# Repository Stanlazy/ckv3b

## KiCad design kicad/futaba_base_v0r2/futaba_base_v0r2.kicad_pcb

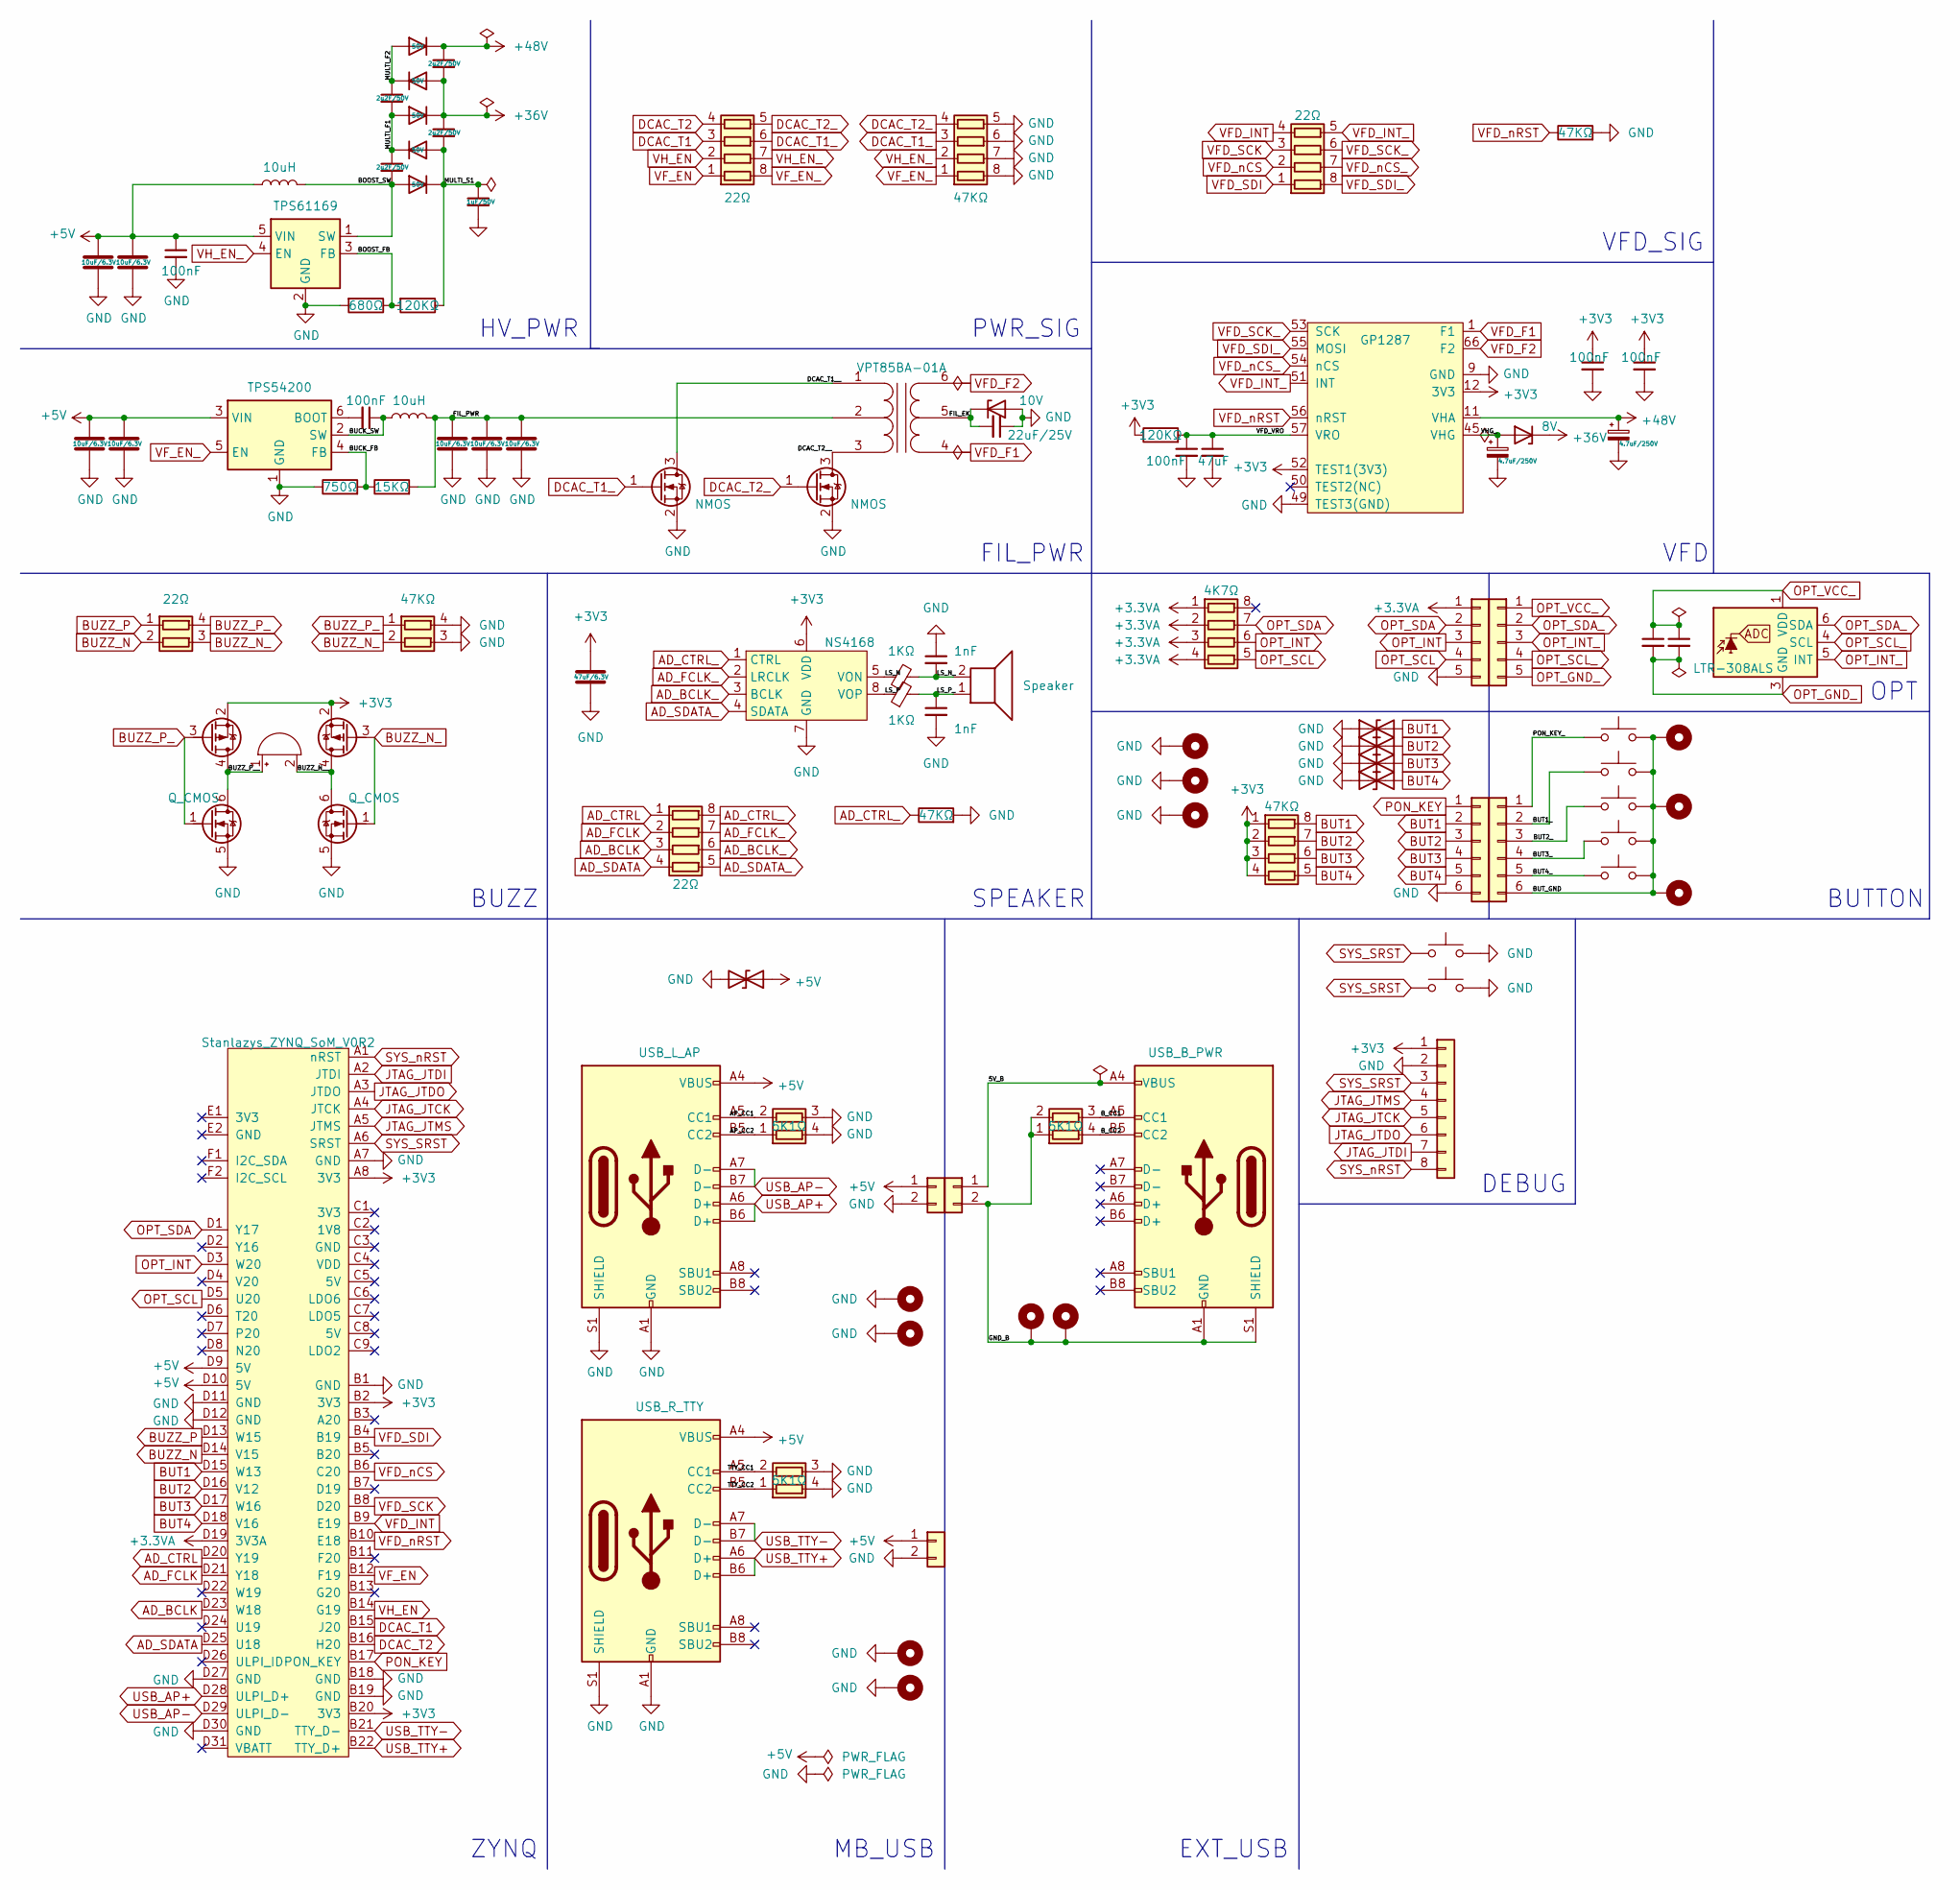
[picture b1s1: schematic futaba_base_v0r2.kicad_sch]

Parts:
A1: Stanlazys_ZYNQ_SoM_V0R2
BZ1: Buzzer; PUIAudio_SMT_0825_S_4_R
C1, C2, C3, C4: 2u2F/50V; C_0805_2012Metric
C5: 1uF/50V; C_0805_2012Metric
C6, C9, C10, C11, C19, C23: 100nF; C_0402_1005Metric
C7, C8, C14, C15, C16, C17, C18: 10uF/6.3V; C_0603_1608Metric
C12: 22uF/25V; C_0805_2012Metric
C13, C21: 4.7uF/250V; CP_Elec_6.3x5.7
C20: 47uF; C_0805_2012Metric
C22: 4u7F; C_0402_1005Metric
C24, C26: 1nF; C_0402_1005Metric
C25: 47uF/6.3V; C_0805_2012Metric
D1, D2, D3, D4, D5: 50V; D_SOD-123F
D6: 10V; D_SOD-123F
D7: 8V; D_SOD-123F
D8, D9, D10, D11: D_TVS; R_0201_0603Metric
D12: D_TVS; D_SOD-323
DS1: GP1287; Futaba_GP1287
FB1, FB2: 1KΩ; L_0402_1005Metric
H1, H2, H3, H4, H5, H6, H7, H8, H9, H10, H11, H12: MountingHole_Pad; MountingHole_PinHeader_2.54_3D
J1: Conn_01x05; opt_mb
J2: Conn_01x05; opt_ph
J3: Conn_01x06; but_mb
J4: Conn_01x06; but_ph
J5: Conn_01x08; PinHeader_1x08_P2.54mm_Vertical
J6: USB_L_AP; USB_C_Receptacle_HRO_TYPE-C-31-M-12
J7, J11: Conn_01x02; usb_mb
J8: Conn_01x02; usb_ph
J9: USB_B_PWR; USB_C_Receptacle_HRO_TYPE-C-31-M-12
J10: USB_R_TTY; USB_C_Receptacle_HRO_TYPE-C-31-M-12
L1, L2: 10uH; L_Abracon_ASPI-0630LR
LS1: Speaker; PinHeader_1x02_P2.54mm_Vertical
Q1, Q2: NMOS; SOT-23
Q3, Q4: Q_CMOS; SOT-23-6
R1, R7: 47KΩ; R_0402_1005Metric
R2: 680Ω; R_0402_1005Metric
R3, R4: 120KΩ; R_0402_1005Metric
R5: 750Ω; R_0402_1005Metric
R6: 15KΩ; R_0402_1005Metric
RN1, RN3, RN7: 22Ω; R_Array_Convex_4x0402
RN2, RN8: 47KΩ; R_Array_Convex_4x0402
RN4: 22Ω; R_Array_Convex_2x0402
RN5: 47KΩ; R_Array_Convex_2x0402
RN6: 4K7Ω; R_Array_Convex_4x0402
RN9, RN10, RN11: 5K1Ω; R_Array_Convex_2x0402
SW1, SW2, SW3, SW4, SW5, SW6: SW_Push; SW_Push_1P1T_NO_6x6mm_H9.5mm
SW7: SW_Push; SW_SPST_CK_RS282G05A3
T1: VPT85BA-01A; VPT85xx
U1: TPS61169; SOT-353_SC-70-5
U2: TPS54200; SOT-23-6
U3: LTR-308ALS
U4: NS4168; HSOP-8-1EP_3.9x4.9mm_P1.27mm_EP2.3x2.3mm

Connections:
+3.3VA: A1.D19 (3V3A), J1.1, RN6.1 (R1.1), RN6.2 (R2.1), RN6.3 (R3.1), RN6.4 (R4.1)
+3V3: A1.A8 (3V3), A1.B2 (3V3), A1.B20 (3V3), C9.1, C10.1, C25.1, DS1.12 (3V3), DS1.52 (TEST1(3V3)), DS1.60 (3V3), J5.1, Q3.2 (S2), Q4.2 (S2), R4.1, RN8.1 (R1.1), RN8.2 (R2.1), RN8.3 (R3.1), RN8.4 (R4.1), U4.6 (VDD)
+5V: A1.D9 (5V), A1.D10 (5V), C6.1, C7.1, C8.1, C14.1, C15.1, D12.1 (A1), J6.A4 (VBUS), J6.A9 (VBUS), J6.B4 (VBUS), J6.B9 (VBUS), J7.1, J10.A4 (VBUS), J10.A9 (VBUS), J10.B4 (VBUS), J10.B9 (VBUS), J11.1, L1.1, U1.5 (VIN), U2.3 (VIN)
+36V: C1.2, C3.1, D2.2 (A), D3.1 (K), D7.1 (K)
+48V: C1.1, C13.1, D1.1 (K), DS1.11 (VHA)
/5V_B: J8.1, J9.A4 (VBUS), J9.A9 (VBUS), J9.B4 (VBUS), J9.B9 (VBUS)
/AP_CC1: J6.A5 (CC1), RN9.2 (R2.1)
/AP_CC2: J6.B5 (CC2), RN9.1 (R1.1)
/BOOST_FB: R2.1, R3.2, U1.3 (FB)
/BOOST_SW: C4.2, D5.2 (A), L1.2, U1.1 (SW)
/BUCK_FB: R5.2, R6.1, U2.4 (FB)
/BUCK_SW: C11.1, L2.1, U2.2 (SW)
/BUT1_: J4.2, SW2.1
/BUT2_: J4.3, SW3.1
/BUT3_: J4.4, SW4.1
/BUT4_: J4.5, SW5.1
/BUT_GND: H1.1, H4.1, H6.1, J4.6, SW1.2, SW2.2, SW3.2, SW4.2, SW5.2
/BUZZ_N__: BZ1.2 (+), Q4.4 (D2), Q4.6 (D1)
/BUZZ_P__: BZ1.1 (-), Q3.4 (D2), Q3.6 (D1)
/B_CC1: J9.A5 (CC1), RN10.3 (R2.2)
/B_CC2: J9.B5 (CC2), RN10.4 (R1.2)
/DCAC_T1__: Q1.3 (D), T1.1 (PR1)
/DCAC_T2__: Q2.3 (D), T1.3 (PR2)
/FIL_EK: C12.2, D6.1 (K), T1.5 (S2)
/FIL_PWR: C16.1, C17.1, C18.1, L2.2, R6.2, T1.2 (PM)
/GND_B: H8.1, H9.1, J8.2, J9.A1 (GND), J9.A12 (GND), J9.B1 (GND), J9.B12 (GND), J9.S1 (SHIELD), RN10.1 (R1.1), RN10.2 (R2.1)
/LS_N: FB1.1, U4.5 (VON)
/LS_N_: C24.2, FB1.2, LS1.2
/LS_P: FB2.1, U4.8 (VOP)
/LS_P_: C26.1, FB2.2, LS1.1
/MULTI_F1: C2.2, C4.1, D3.2 (A), D4.1 (K)
/MULTI_F2: C2.1, D1.2 (A), D2.1 (K)
/MULTI_S1: C3.2, C5.1, D4.2 (A), D5.1 (K), R3.1
/PON_KEY_: J4.1, SW1.1
/TTY_CC1: J10.A5 (CC1), RN11.2 (R2.1)
/TTY_CC2: J10.B5 (CC2), RN11.1 (R1.1)
/VFD_VRO: C19.1, C20.1, DS1.57 (VRO), R4.2
/VHG_: C21.1, D7.2 (A), DS1.45 (VHG)
AD_BCLK: A1.D23 (W18), RN7.3 (R3.1)
AD_BCLK_: RN7.6 (R3.2), U4.3 (BCLK)
AD_CTRL: A1.D20 (Y19), RN7.1 (R1.1)
AD_CTRL_: R7.1, RN7.8 (R1.2), U4.1 (CTRL)
AD_FCLK: A1.D21 (Y18), RN7.2 (R2.1)
AD_FCLK_: RN7.7 (R2.2), U4.2 (LRCLK)
AD_SDATA: A1.D25 (U18), RN7.4 (R4.1)
AD_SDATA_: RN7.5 (R4.2), U4.4 (SDATA)
BUT1: A1.D15 (W13), D8.2 (A2), J3.2, RN8.8 (R1.2)
BUT2: A1.D16 (V12), D9.2 (A2), J3.3, RN8.7 (R2.2)
BUT3: A1.D17 (W16), D10.2 (A2), J3.4, RN8.6 (R3.2)
BUT4: A1.D18 (V16), D11.2 (A2), J3.5, RN8.5 (R4.2)
BUZZ_N: A1.D14 (V15), RN4.2 (R2.1)
BUZZ_N_: Q4.1 (G1), Q4.3 (G2), RN4.3 (R2.2), RN5.2 (R2.1)
BUZZ_P: A1.D13 (W15), RN4.1 (R1.1)
BUZZ_P_: Q3.1 (G1), Q3.3 (G2), RN4.4 (R1.2), RN5.1 (R1.1)
DCAC_T1: A1.B15 (J20), RN1.3 (R3.1)
DCAC_T1_: Q1.1 (G), RN1.6 (R3.2), RN2.3 (R3.1)
DCAC_T2: A1.B16 (H20), RN1.4 (R4.1)
DCAC_T2_: Q2.1 (G), RN1.5 (R4.2), RN2.4 (R4.1)
GND: A1.A7 (GND), A1.B1 (GND), A1.B18 (GND), A1.B19 (GND), A1.D11 (GND), A1.D12 (GND), A1.D27 (GND), A1.D30 (GND), C5.2, C6.2, C7.2, C8.2, C9.2, C10.2, C12.1, C13.2, C14.2, C15.2, C16.2, C17.2, C18.2, C19.2, C20.2, C21.2, C24.1, C25.2, C26.2, D6.2 (A), D8.1 (A1), D9.1 (A1), D10.1 (A1), D11.1 (A1), D12.2 (A2), DS1.9 (GND), DS1.10 (GND), DS1.47 (GND), DS1.49 (TEST3(GND)), DS1.61 (GND), H2.1, H3.1, H5.1, H7.1, H10.1, H11.1, H12.1, J1.5, J3.6, J5.2, J6.A1 (GND), J6.A12 (GND), J6.B1 (GND), J6.B12 (GND), J6.S1 (SHIELD), J7.2, J10.A1 (GND), J10.A12 (GND), J10.B1 (GND), J10.B12 (GND), J10.S1 (SHIELD), J11.2, Q1.2 (S), Q2.2 (S), Q3.5 (S1), Q4.5 (S1), R1.2, R2.2, R5.1, R7.2, RN2.5 (R4.2), RN2.6 (R3.2), RN2.7 (R2.2), RN2.8 (R1.2), RN5.3 (R2.2), RN5.4 (R1.2), RN9.3 (R2.2), RN9.4 (R1.2), RN11.3 (R2.2), RN11.4 (R1.2), SW6.2, SW7.2, U1.2 (GND), U2.1 (GND), U4.7 (GND), U4.9 (GND)
JTAG_JTCK: A1.A4 (JTCK), J5.5
JTAG_JTDI: A1.A2 (JTDI), J5.7
JTAG_JTDO: A1.A3 (JTDO), J5.6
JTAG_JTMS: A1.A5 (JTMS), J5.4
unnamed: C11.2, U2.6 (BOOT)
OPT_GND_: C22.2, C23.2, J2.5, U3.3 (GND)
OPT_INT: A1.D3 (W20), J1.3, RN6.6 (R3.2)
OPT_INT_: J2.3, U3.5 (INT)
OPT_SCL: A1.D5 (U20), J1.4, RN6.5 (R4.2)
OPT_SCL_: J2.4, U3.4 (SCL)
OPT_SDA: A1.D1 (Y17), J1.2, RN6.7 (R2.2)
OPT_SDA_: J2.2, U3.6 (SDA)
OPT_VCC_: C22.1, C23.1, J2.1, U3.1 (VDD)
PON_KEY: A1.B17 (PON_KEY), J3.1
SYS_SRST: A1.A6 (SRST), J5.3, SW6.1, SW7.1
SYS_nRST: A1.A1 (nRST), J5.8
USB_AP+: A1.D28 (ULPI_D+), J6.A6 (D+), J6.B6 (D+)
USB_AP-: A1.D29 (ULPI_D-), J6.A7 (D-), J6.B7 (D-)
USB_TTY+: A1.B22 (TTY_D+), J10.A6 (D+), J10.B6 (D+)
USB_TTY-: A1.B21 (TTY_D-), J10.A7 (D-), J10.B7 (D-)
VFD_F1: DS1.1 (F1), DS1.2 (F1), DS1.3 (F1), DS1.4 (F1), T1.4 (S1)
VFD_F2: DS1.66 (F2), DS1.67 (F2), DS1.68 (F2), DS1.69 (F2), T1.6 (S2)
VFD_INT: A1.B9 (E19), RN3.4 (R4.1)
VFD_INT_: DS1.51 (INT), RN3.5 (R4.2)
VFD_SCK: A1.B8 (D20), RN3.3 (R3.1)
VFD_SCK_: DS1.53 (SCK), RN3.6 (R3.2)
VFD_SDI: A1.B4 (B19), RN3.1 (R1.1)
VFD_SDI_: DS1.55 (MOSI), RN3.8 (R1.2)
VFD_nCS: A1.B6 (C20), RN3.2 (R2.1)
VFD_nCS_: DS1.54 (nCS), RN3.7 (R2.2)
VFD_nRST: A1.B10 (E18), DS1.56 (nRST), R1.1
VF_EN: A1.B12 (F19), RN1.1 (R1.1)
VF_EN_: RN1.8 (R1.2), RN2.1 (R1.1), U2.5 (EN)
VH_EN: A1.B14 (G19), RN1.2 (R2.1)
VH_EN_: RN1.7 (R2.2), RN2.2 (R2.1), U1.4 (EN)

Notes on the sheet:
SPEAKER
BUZZ
ZYNQ
DEBUG
VFD
EXT_USB
PWR_SIG
HV_PWR
OPT
MB_USB
FIL_PWR
VFD_SIG
BUTTON

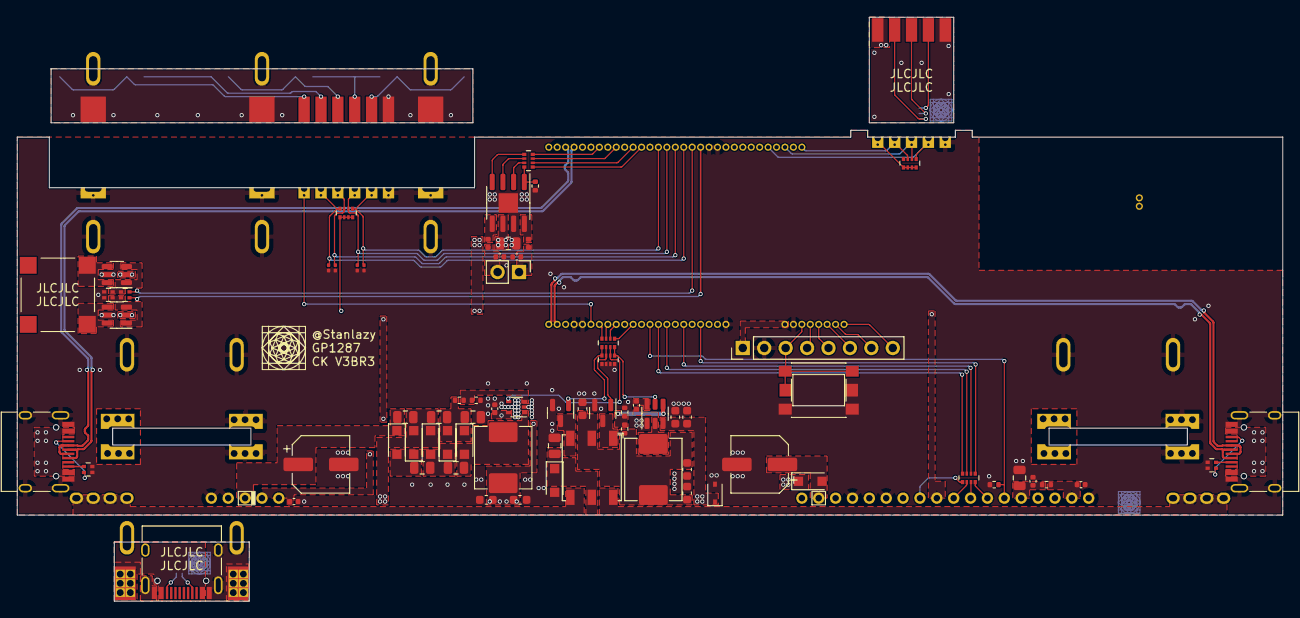
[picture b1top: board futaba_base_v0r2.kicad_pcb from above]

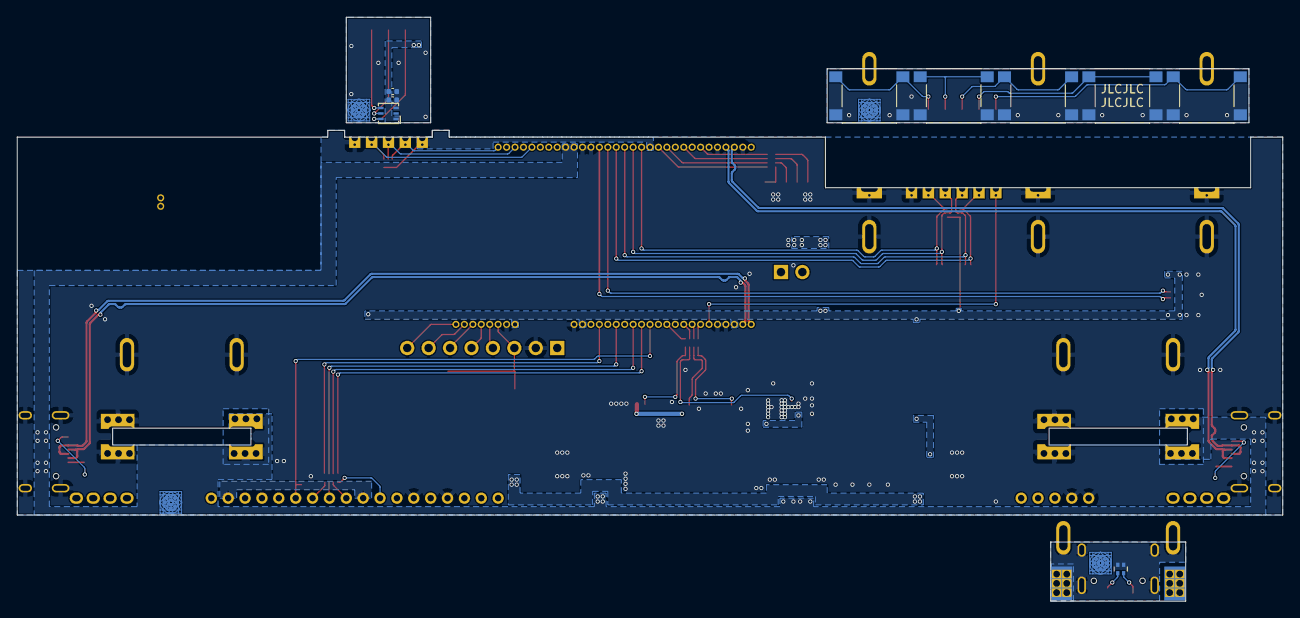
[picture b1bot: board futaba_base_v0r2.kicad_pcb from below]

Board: 2 copper layers, 150.0 x 45.6 mm, 103 parts (11 on the bottom side), 94 nets.

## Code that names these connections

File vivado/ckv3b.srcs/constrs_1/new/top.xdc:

set_property IOSTANDARD LVCMOS33 [get_ports LEDR]
set_property IOSTANDARD LVCMOS33 [get_ports LEDG]
set_property IOSTANDARD LVCMOS33 [get_ports LEDB]
set_property IOSTANDARD LVCMOS33 [get_ports LED2]
set_property IOSTANDARD LVCMOS33 [get_ports LED3]
set_property IOSTANDARD LVCMOS33 [get_ports MB_IIC_scl_io]
set_property IOSTANDARD LVCMOS33 [get_ports MB_IIC_sda_io]
set_property IOSTANDARD LVCMOS33 [get_ports TTY_txd]
set_property IOSTANDARD LVCMOS33 [get_ports TTY_rxd]
set_property IOSTANDARD LVCMOS33 [get_ports PMIC_INT]
set_property IOSTANDARD LVCMOS33 [get_ports RTC_INT]
set_property IOSTANDARD LVCMOS33 [get_ports RTC_32K]
set_property IOSTANDARD LVCMOS33 [get_ports BT_txd]
set_property IOSTANDARD LVCMOS33 [get_ports BT_rxd]
set_property IOSTANDARD LVCMOS33 [get_ports WL_EN]
set_property IOSTANDARD LVCMOS33 [get_ports PL_CLK]
set_property PACKAGE_PIN L20 [get_ports LEDR]
set_property PACKAGE_PIN M20 [get_ports LEDG]
set_property PACKAGE_PIN L19 [get_ports LEDB]
set_property PACKAGE_PIN M19 [get_ports LED2]
set_property PACKAGE_PIN Y14 [get_ports LED3]
set_property PACKAGE_PIN M14 [get_ports MB_IIC_scl_io]
set_property PACKAGE_PIN M15 [get_ports MB_IIC_sda_io]
set_property PACKAGE_PIN J19 [get_ports TTY_txd]
set_property PACKAGE_PIN K19 [get_ports TTY_rxd]
set_property PACKAGE_PIN M17 [get_ports PMIC_INT]
set_property PACKAGE_PIN L15 [get_ports RTC_INT]
set_property PACKAGE_PIN L16 [get_ports RTC_32K]
set_property PACKAGE_PIN K16 [get_ports BT_txd]
set_property PACKAGE_PIN J16 [get_ports BT_rxd]
set_property PACKAGE_PIN J14 [get_ports WL_EN]
set_property PACKAGE_PIN H16 [get_ports PL_CLK]
set_property OFFCHIP_TERM NONE [get_ports LEDB]
set_property OFFCHIP_TERM NONE [get_ports LEDG]
set_property OFFCHIP_TERM NONE [get_ports LEDR]
set_property OFFCHIP_TERM NONE [get_ports LED2]
set_property OFFCHIP_TERM NONE [get_ports LED3]
create_clock -period 20.000 -name pl_clk_in [get_ports PL_CLK]
#set_input_jitter pl_clk 0.6

set_property IOSTANDARD LVCMOS33 [get_ports OPT_IIC_scl_io]
set_property IOSTANDARD LVCMOS33 [get_ports OPT_IIC_sda_io]
set_property IOSTANDARD LVCMOS33 [get_ports OPT_INT]
set_property IOSTANDARD LVCMOS33 [get_ports AD_BCLK]
set_property IOSTANDARD LVCMOS33 [get_ports AD_CTRL]
set_property IOSTANDARD LVCMOS33 [get_ports AD_FCLK]
set_property IOSTANDARD LVCMOS33 [get_ports AD_SDATA]
set_property IOSTANDARD LVCMOS33 [get_ports BUZZ_N]
set_property IOSTANDARD LVCMOS33 [get_ports BUZZ_P]
set_property IOSTANDARD LVCMOS33 [get_ports VFD_SCK]
set_property IOSTANDARD LVCMOS33 [get_ports VFD_SDO]
set_property IOSTANDARD LVCMOS33 [get_ports VFD_nCS]
set_property IOSTANDARD LVCMOS33 [get_ports VFD_nRST]
set_property IOSTANDARD LVCMOS33 [get_ports VH_EN]
set_property IOSTANDARD LVCMOS33 [get_ports VF_EN]
set_property IOSTANDARD LVCMOS33 [get_ports VF_T1]
set_property IOSTANDARD LVCMOS33 [get_ports VF_T2]
set_property IOSTANDARD LVCMOS33 [get_ports BUT1]
set_property IOSTANDARD LVCMOS33 [get_ports BUT2]
set_property IOSTANDARD LVCMOS33 [get_ports BUT3]
set_property IOSTANDARD LVCMOS33 [get_ports BUT4]
set_property IOSTANDARD LVCMOS33 [get_ports VFD_INT]

set_property PACKAGE_PIN U20 [get_ports OPT_IIC_scl_io]
set_property PACKAGE_PIN Y17 [get_ports OPT_IIC_sda_io]
set_property PACKAGE_PIN W20 [get_ports OPT_INT]
set_property PACKAGE_PIN W18 [get_ports AD_BCLK]
set_property PACKAGE_PIN Y19 [get_ports AD_CTRL]
set_property PACKAGE_PIN Y18 [get_ports AD_FCLK]
set_property PACKAGE_PIN U18 [get_ports AD_SDATA]
set_property PACKAGE_PIN V15 [get_ports BUZZ_N]
set_property PACKAGE_PIN W15 [get_ports BUZZ_P]
set_property PACKAGE_PIN D20 [get_ports VFD_SCK]
set_property PACKAGE_PIN B19 [get_ports VFD_SDO]
set_property PACKAGE_PIN C20 [get_ports VFD_nCS]
set_property PACKAGE_PIN E18 [get_ports VFD_nRST]
set_property PACKAGE_PIN G19 [get_ports VH_EN]
set_property PACKAGE_PIN F19 [get_ports VF_EN]
set_property PACKAGE_PIN J20 [get_ports VF_T1]
set_property PACKAGE_PIN H20 [get_ports VF_T2]
set_property PACKAGE_PIN W13 [get_ports BUT1]
set_property PACKAGE_PIN V12 [get_ports BUT2]
set_property PACKAGE_PIN W16 [get_ports BUT3]
set_property PACKAGE_PIN V16 [get_ports BUT4]
set_property PACKAGE_PIN E19 [get_ports VFD_INT]

# set_property SLEW FAST [get_ports VFD_nCS]
# set_property SLEW FAST [get_ports VFD_nRST]
# set_property SLEW FAST [get_ports VFD_SCK]
# set_property SLEW FAST [get_ports VFD_SDO]
# set_property SLEW FAST [get_ports VF_T2]
# set_property SLEW FAST [get_ports VF_T1]
# set_property SLEW FAST [get_ports VH_EN]
# set_property SLEW FAST [get_ports VF_EN]

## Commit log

2023-06-06 add kicad
